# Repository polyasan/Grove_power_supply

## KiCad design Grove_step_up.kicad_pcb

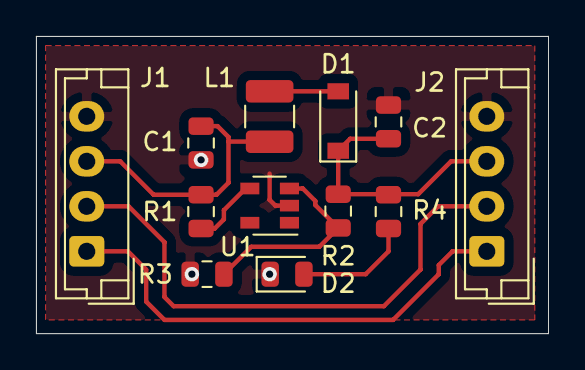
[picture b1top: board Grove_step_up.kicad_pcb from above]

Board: 2 copper layers, 28.4 x 16.5 mm, 12 parts (0 on the bottom side), 9 nets.

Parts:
C1, C2: CP; C_0805_2012Metric
D1: 1N5819; D_SOD-123
D2: LED; LED_0805_2012Metric
J1, J2: Conn_01x04; JST_EH_B4B-EH-A_1x04_P2.50mm_Vertical
L1: L; L_1210_3225Metric
R1, R2, R3, R4: R; R_0805_2012Metric
U1: AP3012; SOT-23-5

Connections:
+3V3: C1.1, J1.3, L1.1, R1.2
+5V: C2.1, D1.1, J2.3, R2.2, R4.1
GND: C1.2, C2.2, D2.1, J1.4, J2.4, R3.2, U1.2
unnamed: D1.2, L1.2
unnamed: D2.2, R4.2
unnamed: J1.1, J2.1
unnamed: J1.2, J2.2
unnamed: R1.1, U1.4
unnamed: R2.1, R3.1, U1.3
